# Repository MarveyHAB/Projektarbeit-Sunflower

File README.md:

Willkommen im Sunflower GitHub Repository:

Der Schaltplan:

Pico W Pinout:

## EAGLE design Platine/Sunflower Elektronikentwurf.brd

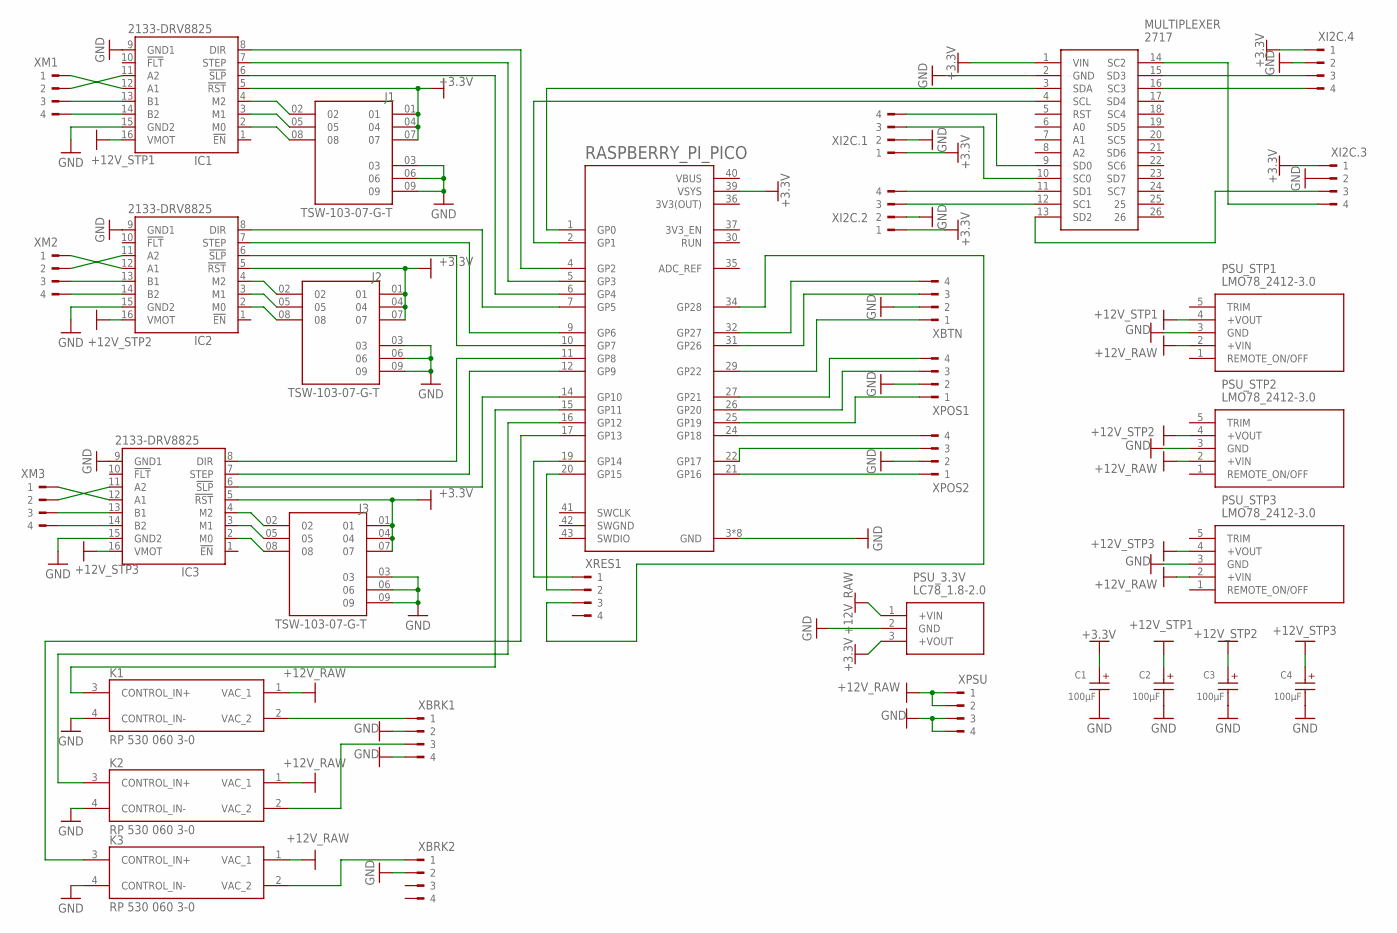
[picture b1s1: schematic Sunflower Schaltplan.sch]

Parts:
C1, C2, C3, C4: 100µF; WCAP-ATET_10X16(DXL)
IC1, IC2, IC3: 2133-DRV8825; DRV8825
J1, J2, J3: TSW-103-07-G-T; SAMTEC_TSW-103-07-G-T
K1, K2, K3: RP 530 060 3-0; RELAY_RP1A23D5
MULTIPLEXER: 2717
PSU_3.3V: LC78_1.8-2.0; LC78_1820; MANUFACTURER_PART_NUMBER LC78_03-2.0
PSU_STP1, PSU_STP2, PSU_STP3: LMO78_2412-3.0; LMO78_241230
RASPBERRY_PI_PICO: RASPBERRY_PICOTH; PICO-PKG-TH
XBRK1, XBRK2: ANLOX_PT09304HBBN
XBTN: ANLOX_PT09304HBBN
XI2C.1, XI2C.2, XI2C.3, XI2C.4: ANLOX_PT09304HBBN
XM1, XM2, XM3: ANLOX_PT09304HBBN
XPOS1, XPOS2: ANLOX_PT09304HBBN
XPSU: ANLOX_PT09304HBBN
XRES1: ANLOX_PT09304HBBN

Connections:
3V3(OUT): RASPBERRY_PI_PICO.36 (3V3(OUT))
+3.3V: C1.1 (+), IC1.5 (!RST), IC2.5 (!RST), IC3.5 (!RST), J1.01, J1.04, J1.07, J2.01, J2.04, J2.07, J3.01, J3.04, J3.07, MULTIPLEXER.1 (VIN), PSU_3.3V.3 (+VOUT), RASPBERRY_PI_PICO.39 (VSYS), XI2C.1.1, XI2C.2.1, XI2C.3.1, XI2C.4.1
+12V_RAW: K1.1 (VAC_1), K2.1 (VAC_1), K3.1 (VAC_1), PSU_3.3V.1 (+VIN), PSU_STP1.2 (+VIN), PSU_STP2.2 (+VIN), PSU_STP3.2 (+VIN), XPSU.1, XPSU.2
+12V_STP1: C2.1 (+), IC1.16 (VMOT), PSU_STP1.4 (+VOUT)
+12V_STP2: C3.1 (+), IC2.16 (VMOT), PSU_STP2.4 (+VOUT)
+12V_STP3: C4.1 (+), IC3.16 (VMOT), PSU_STP3.4 (+VOUT)
GND: C1.2 (-), C2.2 (-), C3.2 (-), C4.2 (-), IC1.9 (GND1), IC1.15 (GND2), IC2.9 (GND1), IC2.15 (GND2), IC3.9 (GND1), IC3.15 (GND2), J1.03, J1.06, J1.09, J2.03, J2.06, J2.09, J3.03, J3.06, J3.09, K1.4 (CONTROL_IN-), K2.4 (CONTROL_IN-), K3.4 (CONTROL_IN-), MULTIPLEXER.2 (GND), PSU_3.3V.2 (GND), PSU_STP1.3 (GND), PSU_STP2.3 (GND), PSU_STP3.3 (GND), RASPBERRY_PI_PICO.3 (GND), RASPBERRY_PI_PICO.8 (GND), RASPBERRY_PI_PICO.13 (GND), RASPBERRY_PI_PICO.18 (GND), RASPBERRY_PI_PICO.23 (GND), RASPBERRY_PI_PICO.28 (GND), RASPBERRY_PI_PICO.33 (GND), RASPBERRY_PI_PICO.38 (GND), XBRK1.2, XBRK1.4, XBRK2.2, XBTN.2, XI2C.1.2, XI2C.2.2, XI2C.3.2, XI2C.4.2, XPOS1.2, XPOS2.2, XPSU.3, XPSU.4
unnamed: MULTIPLEXER.3 (SDA), RASPBERRY_PI_PICO.1 (GP0)
unnamed: MULTIPLEXER.4 (SCL), RASPBERRY_PI_PICO.2 (GP1)
unnamed: IC1.12 (A1), XM1.1
unnamed: IC1.11 (A2), XM1.2
unnamed: IC1.13 (B1), XM1.3
unnamed: IC1.14 (B2), XM1.4
unnamed: IC2.12 (A1), XM2.1
unnamed: IC2.11 (A2), XM2.2
unnamed: IC2.13 (B1), XM2.3
unnamed: IC2.14 (B2), XM2.4
unnamed: IC3.12 (A1), XM3.1
unnamed: IC3.11 (A2), XM3.2
unnamed: IC3.13 (B1), XM3.3
unnamed: IC3.14 (B2), XM3.4
unnamed: IC1.8 (DIR), RASPBERRY_PI_PICO.4 (GP2)
unnamed: IC2.8 (DIR), RASPBERRY_PI_PICO.7 (GP5)
unnamed: IC3.8 (DIR), RASPBERRY_PI_PICO.11 (GP8)
unnamed: IC1.7 (STEP), RASPBERRY_PI_PICO.5 (GP3)
unnamed: IC2.7 (STEP), RASPBERRY_PI_PICO.9 (GP6)
unnamed: IC1.4 (M2), J1.02
unnamed: RASPBERRY_PI_PICO.29 (GP22), XBTN.1
unnamed: RASPBERRY_PI_PICO.31 (GP26), XBTN.3
unnamed: RASPBERRY_PI_PICO.32 (GP27), XBTN.4
unnamed: MULTIPLEXER.9 (SD0), XI2C.1.4
unnamed: MULTIPLEXER.10 (SC0), XI2C.1.3
unnamed: MULTIPLEXER.11 (SD1), XI2C.2.4
unnamed: MULTIPLEXER.12 (SC1), XI2C.2.3
unnamed: MULTIPLEXER.13 (SD2), XI2C.3.3
unnamed: MULTIPLEXER.15 (SD3), XI2C.4.3
unnamed: MULTIPLEXER.14 (SC2), XI2C.3.4
unnamed: MULTIPLEXER.16 (SC3), XI2C.4.4
unnamed: RASPBERRY_PI_PICO.21 (GP16), XPOS2.1
unnamed: RASPBERRY_PI_PICO.22 (GP17), XPOS2.3
unnamed: RASPBERRY_PI_PICO.24 (GP18), XPOS2.4
unnamed: RASPBERRY_PI_PICO.25 (GP19), XPOS1.1
unnamed: RASPBERRY_PI_PICO.26 (GP20), XPOS1.3
unnamed: RASPBERRY_PI_PICO.27 (GP21), XPOS1.4
unnamed: K1.3 (CONTROL_IN+), RASPBERRY_PI_PICO.15 (GP11)
unnamed: K2.3 (CONTROL_IN+), RASPBERRY_PI_PICO.16 (GP12)
unnamed: K3.3 (CONTROL_IN+), RASPBERRY_PI_PICO.17 (GP13)
unnamed: K3.2 (VAC_2), XBRK2.1
unnamed: RASPBERRY_PI_PICO.20 (GP15), XRES1.2
unnamed: RASPBERRY_PI_PICO.19 (GP14), XRES1.1
unnamed: IC3.6 (!SLP), RASPBERRY_PI_PICO.14 (GP10)
unnamed: IC2.6 (!SLP), RASPBERRY_PI_PICO.10 (GP7)
unnamed: K1.2 (VAC_2), XBRK1.1
unnamed: K2.2 (VAC_2), XBRK1.3
unnamed: IC1.6 (!SLP), RASPBERRY_PI_PICO.6 (GP4)
unnamed: RASPBERRY_PI_PICO.34 (GP28), XRES1.3
unnamed: IC1.3 (M1), J1.05
unnamed: IC3.7 (STEP), RASPBERRY_PI_PICO.12 (GP9)
unnamed: IC1.2 (M0), J1.08
unnamed: IC2.4 (M2), J2.02
unnamed: IC2.3 (M1), J2.05
unnamed: IC2.2 (M0), J2.08
unnamed: IC3.4 (M2), J3.02
unnamed: IC3.3 (M1), J3.05
unnamed: IC3.2 (M0), J3.08
SWGND: RASPBERRY_PI_PICO.42 (SWGND)
VBUS: RASPBERRY_PI_PICO.40 (VBUS)

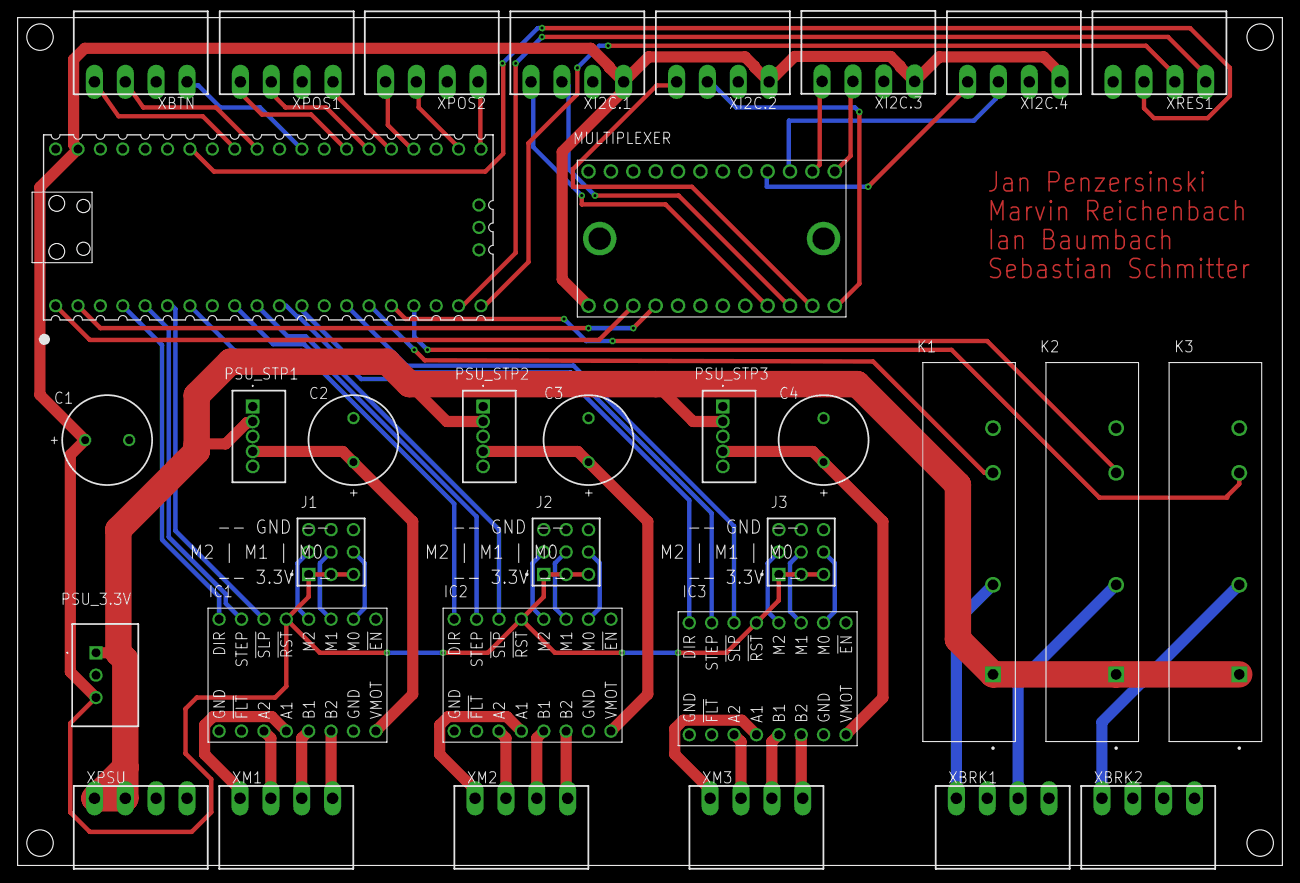
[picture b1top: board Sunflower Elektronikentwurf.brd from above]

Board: 2 copper layers, 143.5 x 96.2 mm, 33 parts (0 on the bottom side), 64 nets.

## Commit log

2023-09-22 Software/Sonne
2023-09-22 Main
2023-10-09 Update main.py
    einmal alles geändert
2023-10-09 Create neigen
2023-10-09 Rename neigen to neigen.py
2023-10-09 Update drehen_ohne_kompass.py
    Bug fixes
2023-10-09 anpassungen VSS
2023-10-10 erste Version faechern.py
    könnte vielleicht funktionieren
2024-01-04 Update expander.py
    Anpassung adressen
2024-01-04 Update expander.py
    schreibfehler
2024-01-08 Update main.py
    erster aufruf der funktionen beim buttondruck
2024-01-12 Update main.py
    local state start
2024-01-17 Update main.py
    Display
2024-01-17 Update main.py
    import display
2024-01-19 Update main.py
    Erstes Testen an Blume
2024-01-22 Update main.py
    ohne timer interrupt
2024-01-22 Update main.py
    bereinigt
2024-01-23 Update faechern.py jetzt mit Endlagen!
2024-01-26 Update main.py
    Mit Kompass
2024-01-27 Update main.py
    Final V1.0
2024-01-27 Final V1.0
2024-01-30 Create löschen
2024-01-30 Rename drehen_ohne_kompass.py to drehen_ohne_kompass.py
2024-01-30 Update faechern.py
    Lesbarkeit verbessert
2024-01-30 Update main.py
    states hinzugefügt
2024-02-03 Update neigen.py
    schreibfehler behoben

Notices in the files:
parts and their libraries:
Wurth_Capacitors_WCAP-ATET: Copyright: Würth Elektronik
